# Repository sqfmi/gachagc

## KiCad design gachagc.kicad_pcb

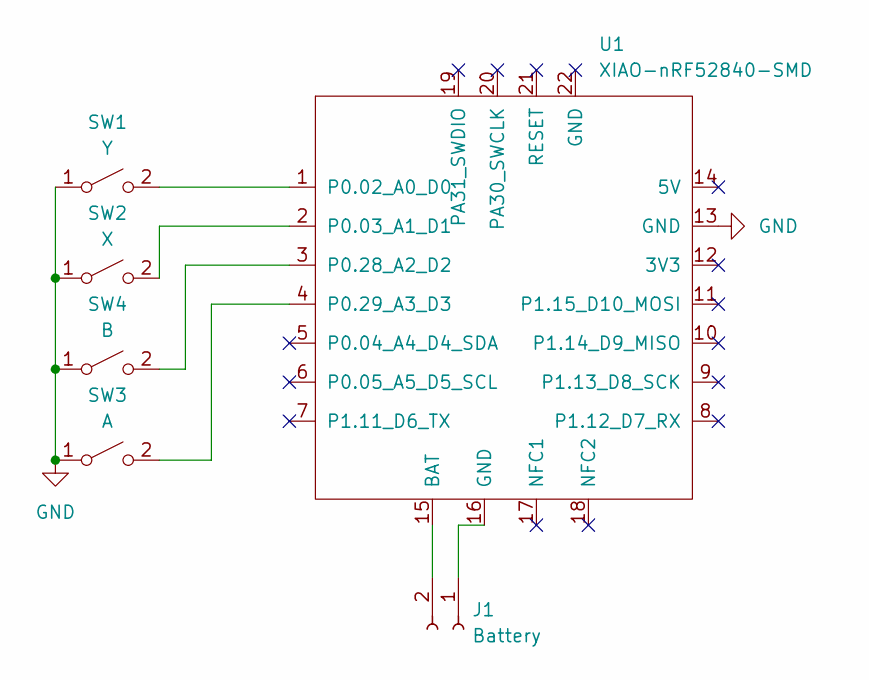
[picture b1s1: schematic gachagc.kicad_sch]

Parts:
J1: Battery; 1.25T-2PWT
SW1: Y; ABXY_Contact
SW2: X; ABXY_Contact
SW3: A; ABXY_Contact
SW4: B; ABXY_Contact
U1: XIAO-nRF52840-SMD

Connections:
GND: SW1.1 (A), SW2.1 (A), SW3.1 (A), SW4.1 (A), U1.13 (GND)
unnamed: J1.1, U1.16 (GND)
unnamed: J1.2, U1.15 (BAT)
unnamed: SW1.2 (B), U1.1 (P0.02_A0_D0)
unnamed: SW2.2 (B), U1.2 (P0.03_A1_D1)
unnamed: SW3.2 (B), U1.4 (P0.29_A3_D3)
unnamed: SW4.2 (B), U1.3 (P0.28_A2_D2)

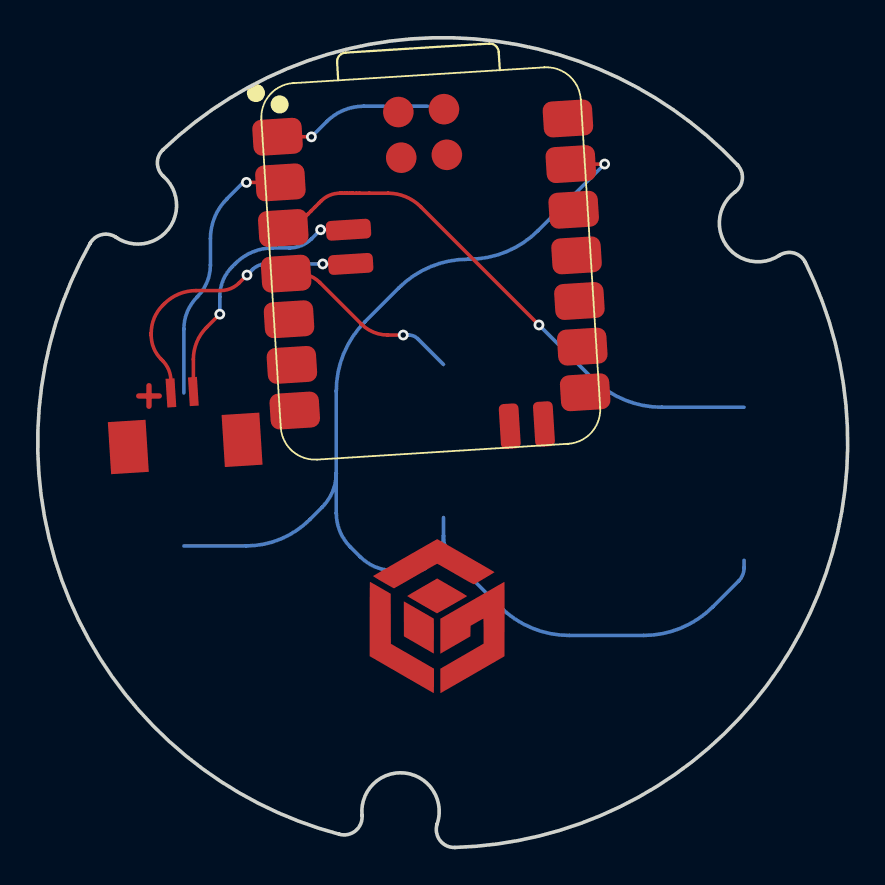
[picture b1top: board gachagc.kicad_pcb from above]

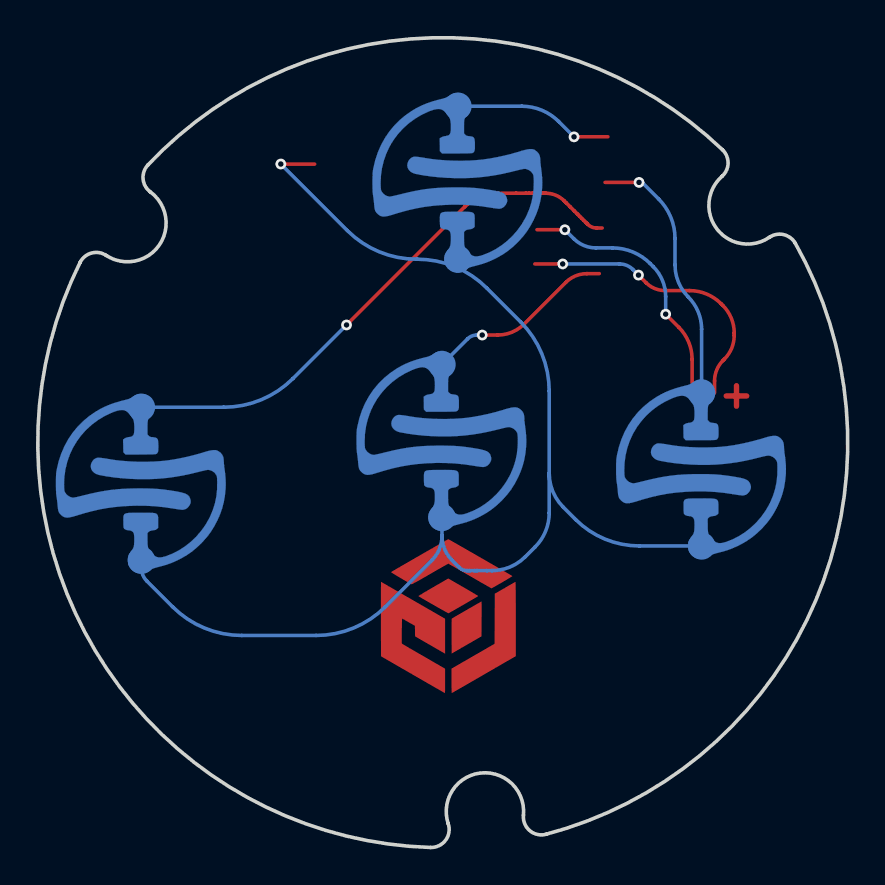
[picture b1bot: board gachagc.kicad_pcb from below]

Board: 2 copper layers, 45.0 x 45.0 mm, 6 parts (4 on the bottom side), 7 nets.
